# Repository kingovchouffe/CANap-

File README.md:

# CANap-
USB to CANbus dongle based on STM32F302

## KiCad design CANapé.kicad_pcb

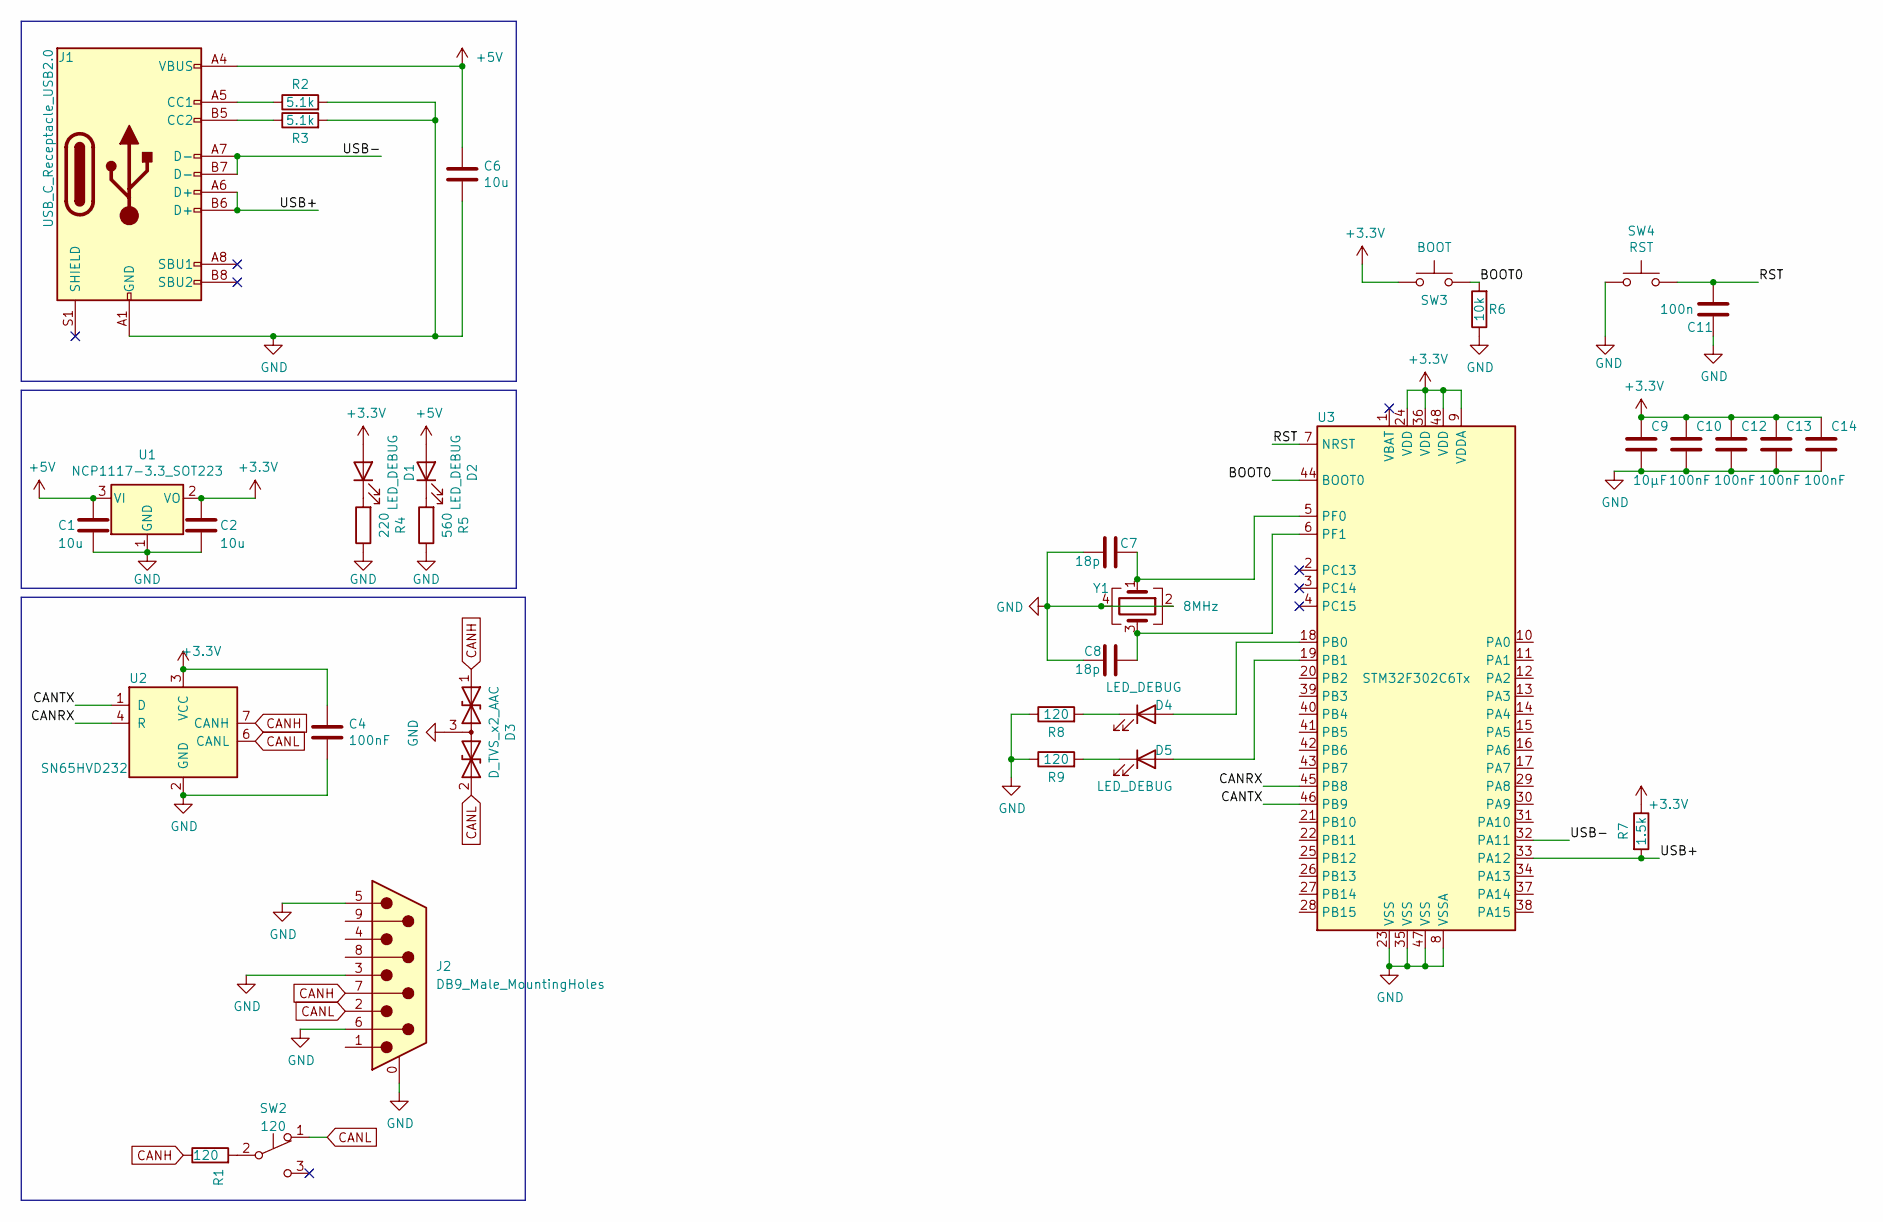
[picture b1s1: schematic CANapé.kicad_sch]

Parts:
C1, C2, C6: 10u; C_0805_2012Metric
C4, C10, C12, C13, C14: 100nF; C_0805_2012Metric
C7, C8: 18p; C_0805_2012Metric
C9: 10µF; C_0805_2012Metric
C11: 100n; C_0805_2012Metric
D1, D2, D4, D5: LED_DEBUG; LED_0805_2012Metric
D3: D_TVS_x2_AAC; SOT-23
J1: USB_C_Receptacle_USB2.0; USB_C_Receptacle_GCT_USB4085
J2: DB9_Male_MountingHoles; DSUB-9_Male_Horizontal_P2.77x2.84mm_EdgePinOffset7.70mm_Hou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
R1, R8, R9: 120; R_0805_2012Metric
R2, R3: 5.1k; R_0805_2012Metric
R4: 220; R_0805_2012Metric
R5: 560; R_0805_2012Metric
R6: 10k; R_0805_2012Metric
R7: 1.5k; R_0805_2012Metric
SW2: 120; SW_Push_1P2T_Vertical_E-Switch_800UDP8P1A1M6
SW3: BOOT; SW_SPST_CK_RS282G05A3
SW4: RST; SW_SPST_CK_RS282G05A3
U1: NCP1117-3.3_SOT223; SOT-223-3_TabPin2
U2: SN65HVD232; SOIC-8_3.9x4.9mm_P1.27mm
U3: STM32F302C6Tx; LQFP-48_7x7mm_P0.5mm
Y1: 8MHz; Crystal_SMD_5032-4Pin_5.0x3.2mm

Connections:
+3V3: C2.2, C4.2, C9.2, C10.2, C12.2, C13.2, C14.2, D1.2 (A), R7.1, SW3.1, U1.2 (VO), U2.3 (VCC), U3.9 (VDDA), U3.24 (VDD), U3.36 (VDD), U3.48 (VDD)
+5V: C1.2, C6.1, D2.2 (A), J1.A4 (VBUS), J1.A9 (VBUS), J1.B4 (VBUS), J1.B9 (VBUS), U1.3 (VI)
/BOOT0: R6.2, SW3.2, U3.44 (BOOT0)
/CANRX: U2.4 (R), U3.45 (PB8)
/CANTX: U2.1 (D), U3.46 (PB9)
/RST: C11.1, SW4.2, U3.7 (NRST)
/USB+: J1.A6 (D+), J1.B6 (D+), R7.2, U3.33 (PA12)
/USB-: J1.A7 (D-), J1.B7 (D-), U3.32 (PA11)
CANH: D3.1 (A1), J2.7, R1.1, U2.7 (CANH)
CANL: D3.2 (A2), J2.2, SW2.1 (A), U2.6 (CANL)
GND: C1.1, C2.1, C4.1, C6.2, C7.2, C8.2, C9.1, C10.1, C11.2, C12.1, C13.1, C14.1, D3.3 (common), J1.A1 (GND), J1.A12 (GND), J1.B1 (GND), J1.B12 (GND), J2.0 (PAD), J2.3, J2.5, J2.6, R2.2, R3.2, R4.1, R5.1, R6.1, R8.1, R9.1, SW4.1, U1.1 (GND), U2.2 (GND), U3.8 (VSSA), U3.23 (VSS), U3.35 (VSS), U3.47 (VSS), Y1.2, Y1.4
unnamed: C7.1, U3.5 (PF0), Y1.1
unnamed: C8.1, U3.6 (PF1), Y1.3
unnamed: D1.1 (K), R4.2
unnamed: D2.1 (K), R5.2
unnamed: D4.1 (K), R8.2
unnamed: D4.2 (A), U3.18 (PB0)
unnamed: D5.1 (K), R9.2
unnamed: D5.2 (A), U3.19 (PB1)
unnamed: J1.A5 (CC1), R2.1
unnamed: J1.B5 (CC2), R3.1
unnamed: R1.2, SW2.2 (B)

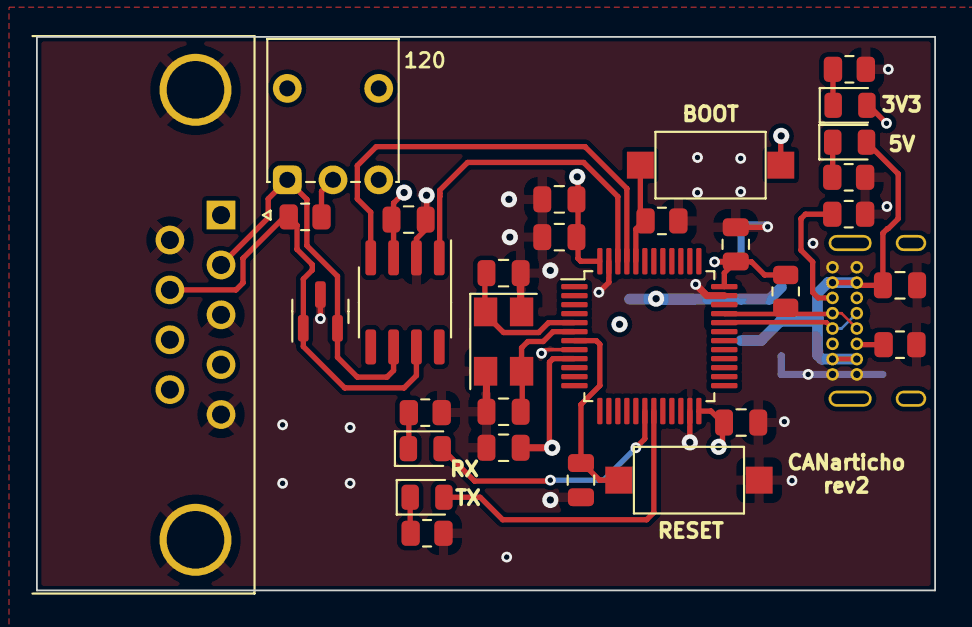
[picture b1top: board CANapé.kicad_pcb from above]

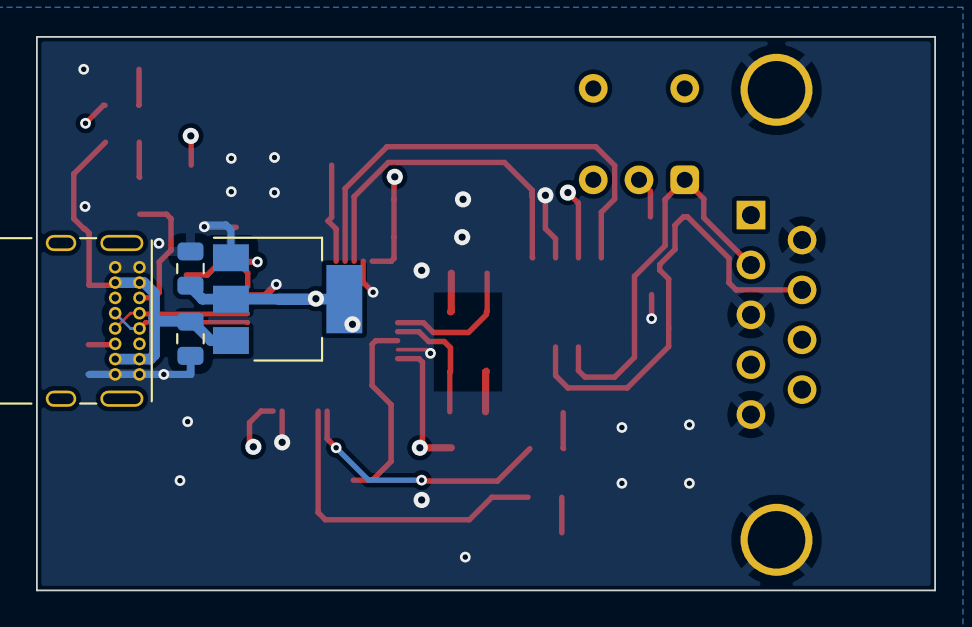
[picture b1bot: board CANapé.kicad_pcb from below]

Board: 4 copper layers, 49.9 x 30.8 mm, 35 parts (4 on the bottom side), 22 nets.

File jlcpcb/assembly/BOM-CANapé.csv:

Comment,Designator,Footprint,LCSC
120,R9,R_0805_2012Metric,
120,R8,R_0805_2012Metric,
1.5k,R7,R_0805_2012Metric,
10k,R6,R_0805_2012Metric,
560,R5,R_0805_2012Metric,
220,R4,R_0805_2012Metric,
5.1k,R3,R_0805_2012Metric,
5.1k,R2,R_0805_2012Metric,
120,R1,R_0805_2012Metric,
DB9_Male_MountingHoles,J2,DSUB-9_Male_Horizontal_P2.77x2.84mm_EdgePinOffset7.70mm_Housed_MountingHolesOffset9.12mm,
LED_DEBUG,D5,LED_0805_2012Metric,
LED_DEBUG,D4,LED_0805_2012Metric,
LED_DEBUG,D2,LED_0805_2012Metric,
LED_DEBUG,D1,LED_0805_2012Metric,
100nF,C14,C_0805_2012Metric,
100nF,C13,C_0805_2012Metric,
100nF,C12,C_0805_2012Metric,
100n,C11,C_0805_2012Metric,
100nF,C10,C_0805_2012Metric,
10µF,C9,C_0805_2012Metric,
18p,C8,C_0805_2012Metric,
18p,C7,C_0805_2012Metric,
10u,C6,C_0805_2012Metric,
100nF,C4,C_0805_2012Metric,
10u,C2,C_0805_2012Metric,
10u,C1,C_0805_2012Metric,
STM32F302C6Tx,U3,LQFP-48_7x7mm_P0.5mm,
BOOT,SW3,SW_SPST_CK_RS282G05A3,
120,SW2,SW_Push_1P2T_Vertical_E-Switch_800UDP8P1A1M6,
SN65HVD232,U2,SOIC-8_3.9x4.9mm_P1.27mm,
D_TVS_x2_AAC,D3,SOT-23,
RST,SW4,SW_SPST_CK_RS282G05A3,
8MHz,Y1,Crystal_SMD_5032-4Pin_5.0x3.2mm,
USB_C_Receptacle_USB2.0,J1,USB_C_Receptacle_GCT_USB4085,
NCP1117-3.3_SOT223,U1,SOT-223-3_TabPin2,

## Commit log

2022-06-28 update silkscreen
2022-06-28 add pdf
2022-11-26 v2 with db9 connector
